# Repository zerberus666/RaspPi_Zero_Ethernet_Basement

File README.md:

# RaspPi_Zero_Ethernet_Basement
Raspberry Pi Zero Ethernet Basement on ENC28J60 chip

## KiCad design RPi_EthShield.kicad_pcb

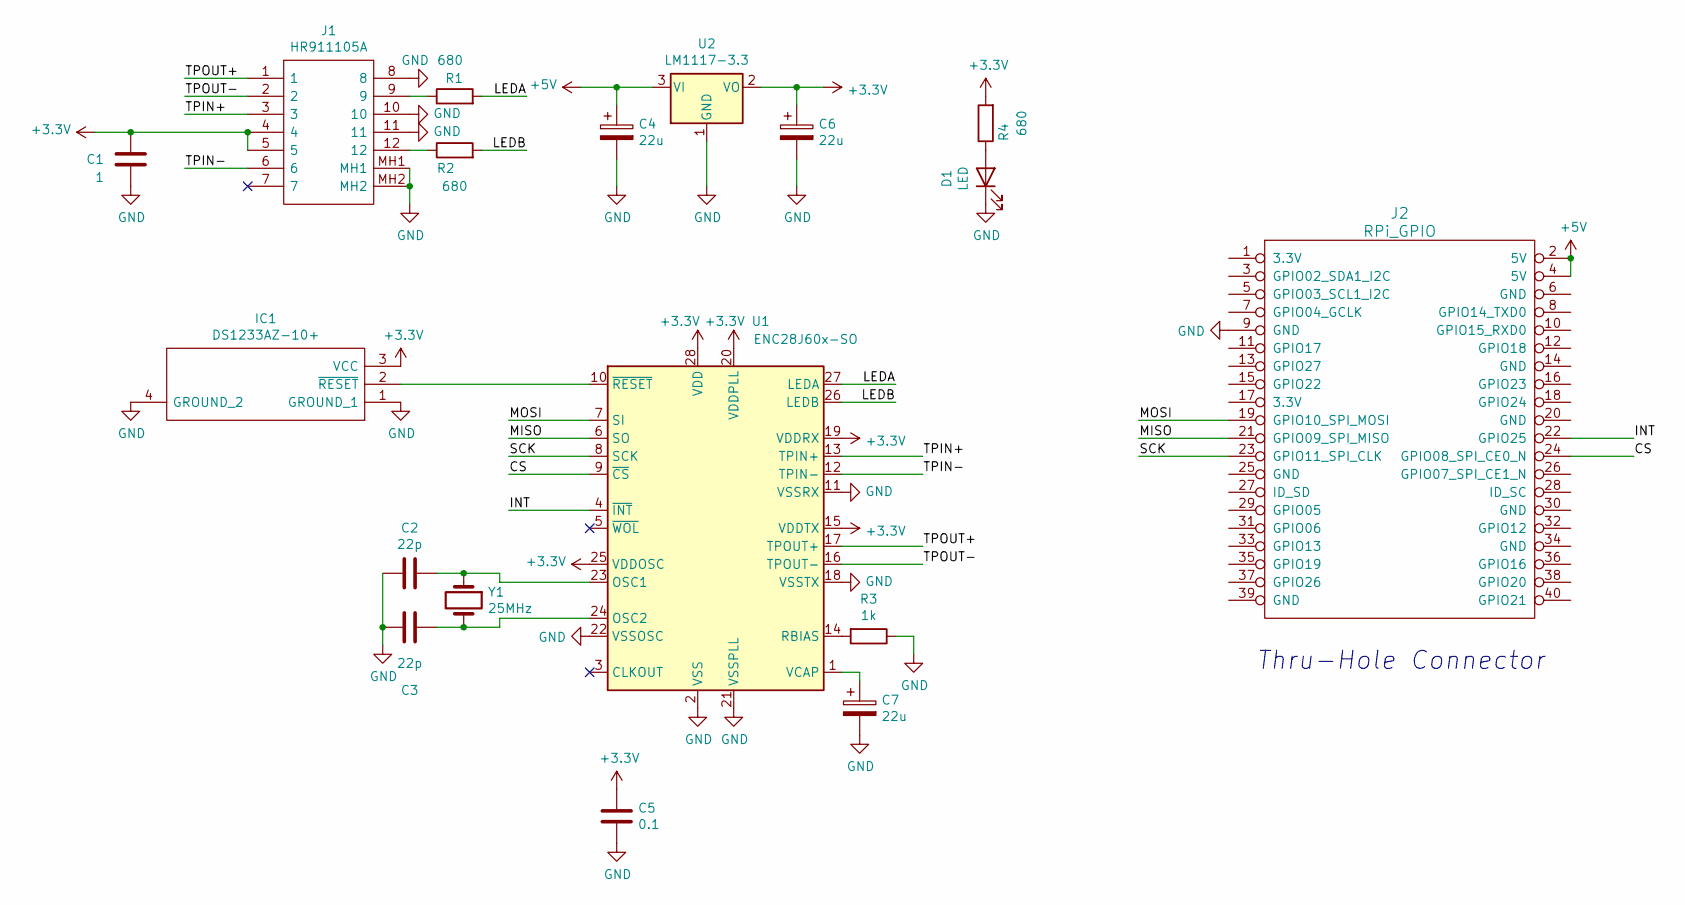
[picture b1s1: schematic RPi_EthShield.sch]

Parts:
C1: 1; C_0805_2012Metric
C2, C3: 22p; C_0805_2012Metric
C4, C6, C7: 22u; C_Elec_5x5.4
C5: 0.1; C_0805_2012Metric
D1: LED; LED_0603_1608Metric
IC1: DS1233AZ-10+; DS1233_SOT223; Manufacturer_Part_Number DS1233AZ-10+; Mouser Part Number 700-DS1233AZ-10
J1: HR911105A; Manufacturer_Part_Number HR911105A
J2: RPi_GPIO; PinHeader_2x20_P2.54mm_Vertical
R1, R2, R4: 680; R_0805_2012Metric
R3: 1k; R_0805_2012Metric
U1: ENC28J60x-SO; SOIC-28W_7.5x17.9mm_P1.27mm
U2: LM1117-3.3; SOT-223
Y1: 25MHz; Crystal_SMD_HC49-SD

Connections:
+3V3: C1.1, C5.1, C6.1, IC1.3 (VCC), J1.4, J1.5, R4.2, U1.15 (VDDTX), U1.19 (VDDRX), U1.20 (VDDPLL), U1.25 (VDDOSC), U1.28 (VDD), U2.2 (VO)
+5V: C4.1, J2.2 (5V), J2.4 (5V), U2.3 (VI)
/CS: J2.24 (GPIO08_SPI_CE0_N), U1.9 (~CS)
/INT: J2.22 (GPIO25), U1.4 (~INT)
/LEDA: R1.2, U1.27 (LEDA)
/LEDB: R2.2, U1.26 (LEDB)
/MISO: J2.21 (GPIO09_SPI_MISO), U1.6 (SO)
/MOSI: J2.19 (GPIO10_SPI_MOSI), U1.7 (SI)
/SCK: J2.23 (GPIO11_SPI_CLK), U1.8 (SCK)
/TPIN+: J1.3, U1.13 (TPIN+)
/TPIN-: J1.6, U1.12 (TPIN-)
/TPOUT+: J1.1, U1.17 (TPOUT+)
/TPOUT-: J1.2, U1.16 (TPOUT-)
GND: C1.2, C2.2, C3.1, C4.2, C5.2, C6.2, C7.2, D1.1 (K), IC1.1 (GROUND_1), IC1.4 (GROUND_2), J1.8, J1.10, J1.11, J1.MH1, J1.MH2, J2.9 (GND), R3.1, U1.2 (VSS), U1.11 (VSSRX), U1.18 (VSSTX), U1.21 (VSSPLL), U1.22 (VSSOSC), U2.1 (GND)
unnamed: C2.1, U1.23 (OSC1), Y1.1
unnamed: C3.2, U1.24 (OSC2), Y1.2
unnamed: C7.1, U1.1 (VCAP)
unnamed: D1.2 (A), R4.1
unnamed: IC1.2 (~RESET), U1.10 (~RESET)
unnamed: J1.9, R1.1
unnamed: J1.12, R2.1
unnamed: R3.2, U1.14 (RBIAS)

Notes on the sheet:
Thru-Hole Connector

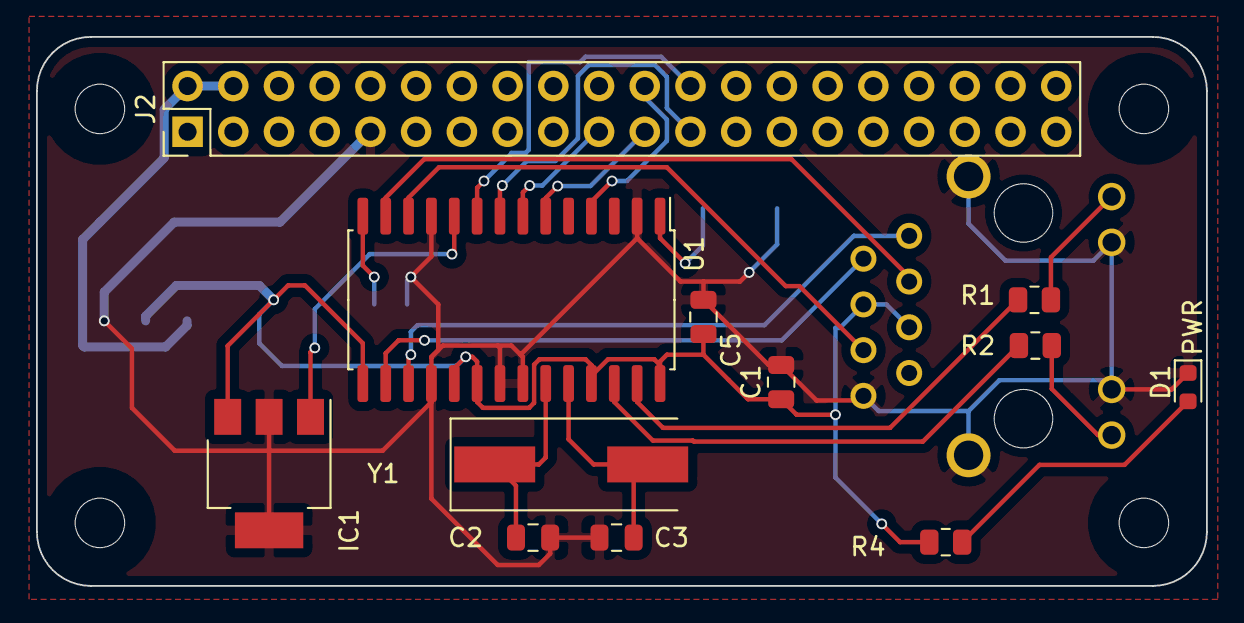
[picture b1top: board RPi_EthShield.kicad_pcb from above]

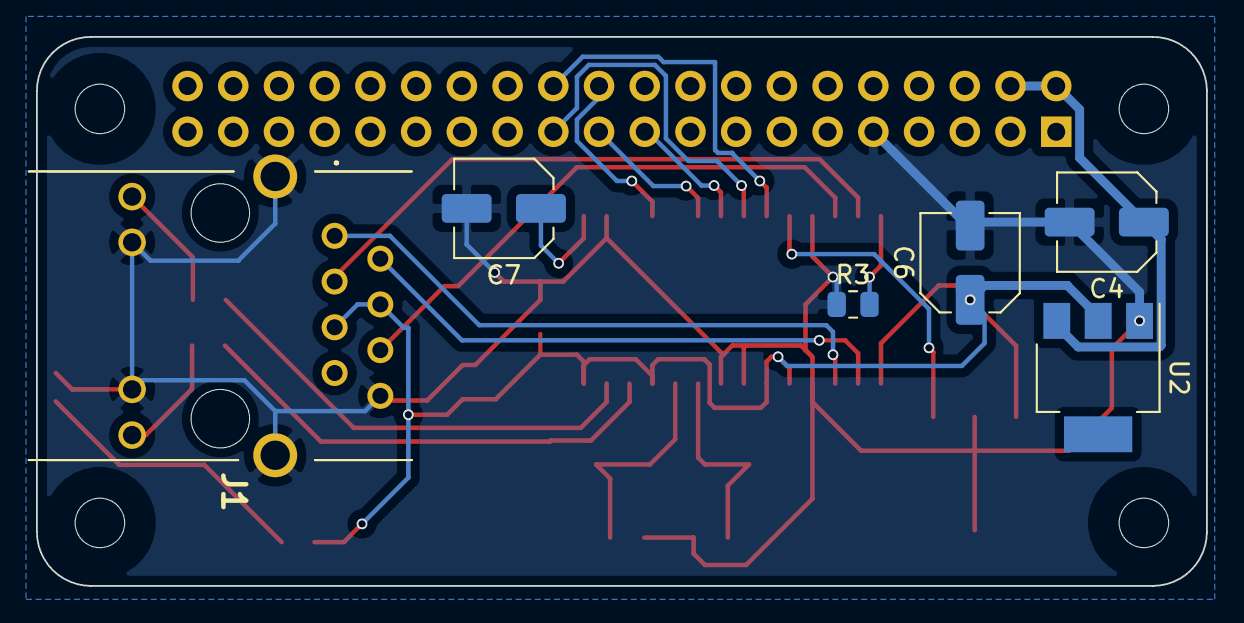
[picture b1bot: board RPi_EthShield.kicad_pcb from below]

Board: 2 copper layers, 65.0 x 30.5 mm, 18 parts (6 on the bottom side), 22 nets.

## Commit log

2021-08-26 Gerber files added
2021-08-26 some small changes in PCB
2021-09-02 Some parts changed
2021-11-02 some changes
2022-01-14 footprint for DS1233a fixed
